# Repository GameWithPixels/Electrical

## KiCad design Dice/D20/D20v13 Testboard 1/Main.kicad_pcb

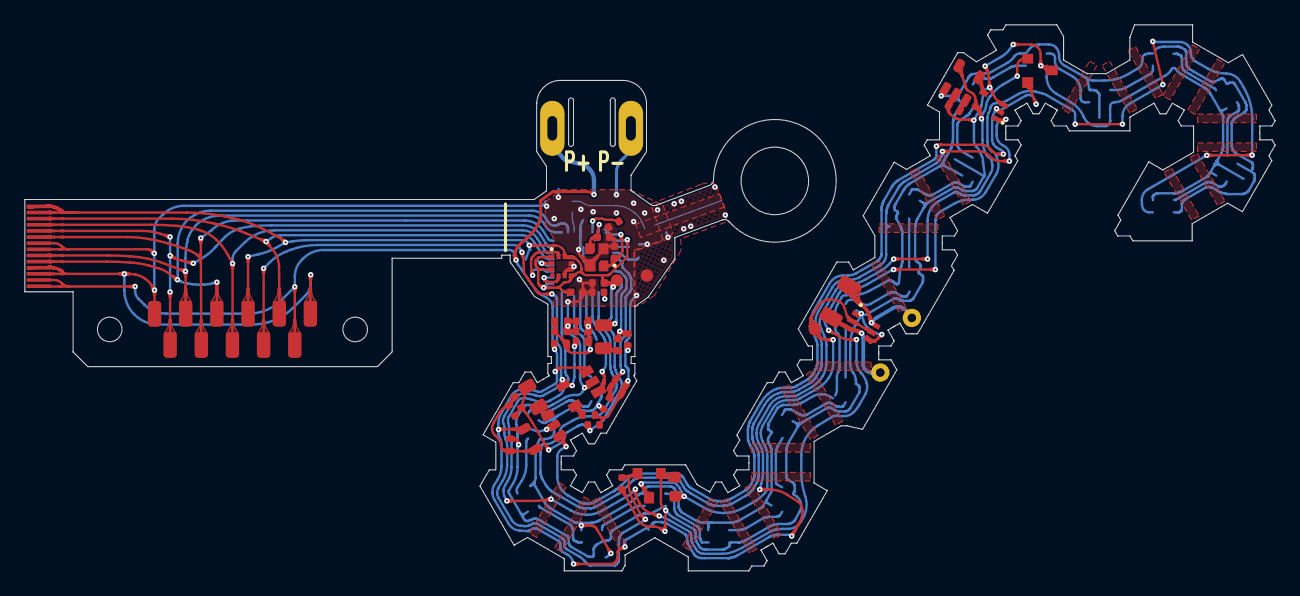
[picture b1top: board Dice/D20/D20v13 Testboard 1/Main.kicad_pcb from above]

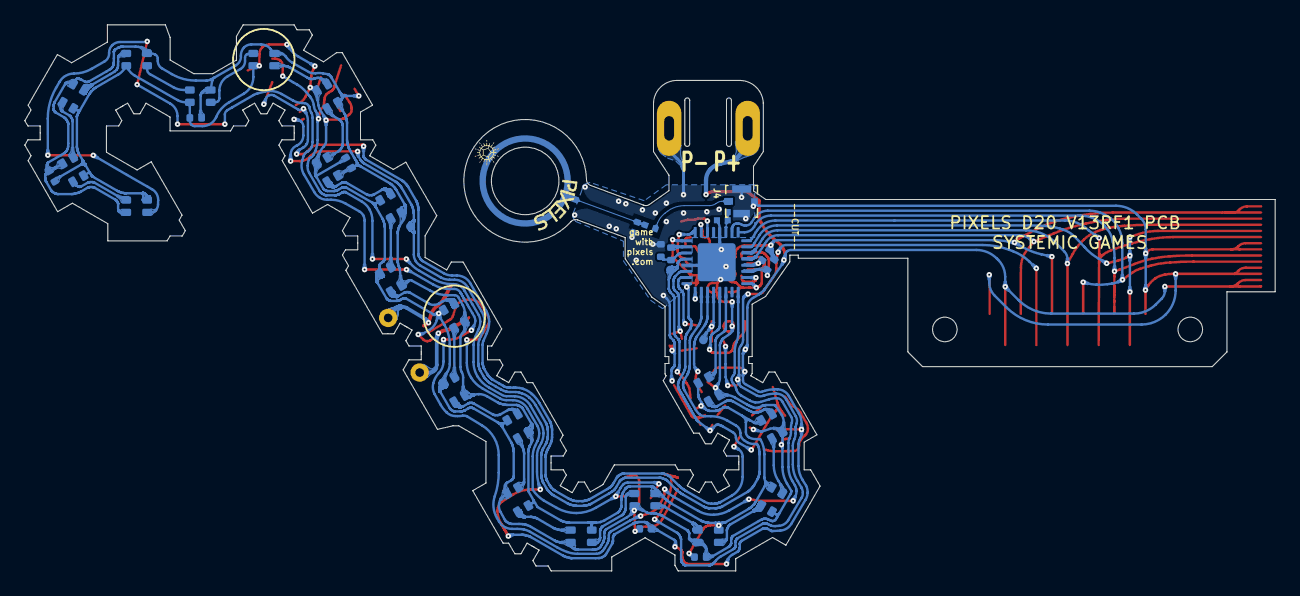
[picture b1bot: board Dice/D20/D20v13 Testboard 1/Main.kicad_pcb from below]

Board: 2 copper layers, 101.9 x 44.5 mm, 84 parts (40 on the bottom side), 61 nets.

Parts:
AE2: ARC; ARC_Antenna
C1, C4, C9, C15, C16, C18: 4.7uF 6.3V 20%; C_0402_1005Metric
C2, C5: 8pF 10V 10%; C_0402_1005Metric
C3, C10, C23, C24, C25: 0.1uF 10V 20%; C_0402_1005Metric
C6, C21, C22: 10nF 25V 10%; C_0402_1005Metric
C7: 100pF NP0 10V 5%; C_0402_1005Metric
C8: 0.8pF 10V 5% NP0; 0402_RF
C11: 1.8pF 10V 5% NP0; 0402_RF
C13: 4.7uF 25V 20%; C_0603_1608Metric
C17: 22pF 10V 5%; C_0402_1005Metric
C19: 33nF 50V 5% NP0; C_1206_3216Metric
D1: BAV99S; SOT-363_SC-70-6
D2, D3, D4, D5, D6, D7, D8, D9, D10, D11, D12, D13, D14, D15, D16, D17, D18, D19, D20, D21: TX1812Z_2020
J1: Conn_01x14; FPC_14
J2: Conn_01x11; FPC-POGO-11
J3: Conn_01x02; Hongjie 10100 Connector
J4: RECE.20369.001E.01; MFH3.RECE.20369.001E.01
L1: 10uH 100mA 10%; L_0805_2012Metric
L2: 15nH 100mA 5%; L_0402_1005Metric
L3: 4.7nH 5%; 0402_RF
L4: 2.2uH 20mA 10%; L_0805_2012Metric
L5: 3.9nH 5%; 0402_RF
P5: COILA; TestPoint_THTPad_D1.5mm_Drill0.7mm
P6: COILB; TestPoint_THTPad_D1.5mm_Drill0.7mm
R1, R7, R13: 4.02M 1%; R_0402_1005Metric
R2, R8, R14: 10M 1%; R_0402_1005Metric
R3: 10k 5%; R_0402_1005Metric
R4: 402k 1%; R_0402_1005Metric
R5, R9, R10: 100k 1%; R_0402_1005Metric
R6: 22k 1%; R_0402_1005Metric
R12, R16: 2.7k 5%; R_0402_1005Metric
U1: N52810_QFN32; QFN-32-1EP_5x5mm_P0.5mm_EP3.1x3.1mm
U2: KXTJ3-1057; LGA-12_2x2mm_P0.5mm
U3: PJ75AL50SA; SOT-23
U4: LN3435; SOT-23-5
U5: MCP73832T-2ACI/OT; SOT-23-5
U6: MT9700; SOT-23-5
U7: 74AHC1G08; SOT-353_SC-70-5
U8: TMR1366; SOT-23
W5: LED_EN; TEST_PIN
W12: VLED_S; TEST_PIN
W13: 5V_S; TEST_PIN
W16: VIN; TEST_PIN
W19: GND; TEST_PIN
W25: VDD; TEST_PIN
Y1: 32MHz 40ppm; Crystal_SMD_2016-4Pin_2.0x1.6mm

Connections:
+5V: C15.1, J2.4, R1.1, U3.2 (VOUT), U5.4 (VDD)
+BATT: C16.1, J1.1, J1.2, J2.2, J3.1, R7.1, U4.4 (VIN), U5.3 (VBAT), U6.5 (VIN), U7.5 (VCC), U8.1 (VCC)
/5V_SENSE: C21.1, R1.2, R2.2, U1.4 (P0.04/AIN2), W13.1
/ACC_INT: U1.10 (P0.12), U2.5 (INT)
/ANT_50: J4.4, L3.1, L5.2
/ANT_NRF: C8.1, L5.1, U1.19 (ANT)
/ARC_ANTENNA: AE2.1 (A), C11.1, L3.2
/LED_DATA: D2.1 (DIN), U1.6 (P0.06)
/LED_EN: U1.2 (P0.00/XL1), U7.1, W5.1
/LEDs/LED_RETURN: D21.3 (DOUT), U1.8 (P0.10)
/Power Supply/LED_EN_OUT: U6.4 (EN), U7.4
/Power Supply/MAG1_: U4.1 (CE), U7.2, U8.2 (OUT)
/SCL: R12.2, U1.11 (P0.14), U2.12 (SCL)
/SDA: R16.2, U1.12 (P0.15), U2.2 (SDA)
/STATS: U1.3 (P0.01/XL2), U5.1 (STAT)
/VBAT_SENSE: C22.1, R7.2, R8.1, U1.5 (P0.05/AIN3)
/VLED_SENSE: C6.1, R13.2, R14.1, U1.28 (P0.30/AIN6), W12.1
GND: C1.2, C2.1, C3.2, C4.2, C5.1, C6.2, C7.2, C8.2, C9.2, C10.2, C11.2, C13.2, C15.2, C16.2, C18.2, C21.2, C22.2, C23.2, C24.2, C25.2, D1.1 (A1), D1.4 (A3), D2.4 (GND), D3.4 (GND), D4.4 (GND), D5.4 (GND), D6.4 (GND), D7.4 (GND), D8.4 (GND), D9.4 (GND), D10.4 (GND), D11.4 (GND), D12.4 (GND), D13.4 (GND), D14.4 (GND), D15.4 (GND), D16.4 (GND), D17.4 (GND), D18.4 (GND), D19.4 (GND), D20.4 (GND), D21.4 (GND), J1.3, J1.4, J1.7, J1.8, J2.1, J2.11, J3.2, J4.1, J4.2, J4.3, R2.1, R3.2, R5.1, R6.2, R8.2, R9.1, R14.2, U1.20 (VSS), U1.29 (VSS), U1.33 (VSS), U2.6 (GND), U2.8 (GND), U2.9 (GND), U3.1 (VSS), U4.2 (GND), U5.2 (VSS), U6.2 (GND), U7.3 (GND), U8.3 (GND), W19.1, Y1.2, Y1.4
unnamed: C1.1, L2.2, U1.30 (DEC4)
unnamed: C2.2, U1.24 (XC2), Y1.1
unnamed: C3.1, U1.1 (DEC1)
unnamed: C5.2, U1.23 (XC1), Y1.3
unnamed: C7.1, U1.22 (DEC3)
unnamed: C17.2, R4.1, R5.2, U4.5 (FB)
unnamed: C19.1, D1.3 (K1A2), P5.1
unnamed: C19.2, D1.6 (K3A4), P6.1
unnamed: D2.3 (DOUT), D3.1 (DIN)
unnamed: D3.3 (DOUT), D4.1 (DIN)
unnamed: D4.3 (DOUT), D5.1 (DIN)
unnamed: D5.3 (DOUT), D6.1 (DIN)
unnamed: D6.3 (DOUT), D7.1 (DIN)
unnamed: D7.3 (DOUT), D8.1 (DIN)
unnamed: D8.3 (DOUT), D9.1 (DIN)
unnamed: D9.3 (DOUT), D10.1 (DIN)
unnamed: D10.3 (DOUT), D11.1 (DIN)
unnamed: D11.3 (DOUT), D12.1 (DIN)
unnamed: D12.3 (DOUT), D13.1 (DIN)
unnamed: D13.3 (DOUT), D14.1 (DIN)
unnamed: D14.3 (DOUT), D15.1 (DIN)
unnamed: D15.3 (DOUT), D16.1 (DIN)
unnamed: D16.3 (DOUT), D17.1 (DIN)
unnamed: D17.3 (DOUT), D18.1 (DIN)
unnamed: D18.3 (DOUT), D19.1 (DIN)
unnamed: D19.3 (DOUT), D20.1 (DIN)
unnamed: D20.3 (DOUT), D21.1 (DIN)
unnamed: L1.1, U1.31 (DCC)
unnamed: L1.2, L2.1
unnamed: L4.1, U4.3 (LX)
unnamed: R3.1, U6.3 (SET)
unnamed: R6.1, U5.5 (PROG)
unnamed: R9.2, R10.1, U1.27 (P0.28/AIN4)
unnamed: R10.2, U1.26 (P0.25)
RESET: J1.9, J2.8, U1.16 (P0.16)
RXI: J1.10, J2.10, U1.15 (P0.20/TCLK)
SWDCLK: J1.6, J2.9, U1.17 (SWDCLK)
SWDIO: J1.5, J2.7, U1.18 (SWDIO)
SWO: J1.11, J2.6, U1.14 (P0.18/TDATA0)
TXO: J1.12, J2.3, U1.13 (P0.16/TDATA1)
VDC: C9.1, C23.1, C24.1, C25.1, D2.2 (VCC), D3.2 (VCC), D4.2 (VCC), D5.2 (VCC), D6.2 (VCC), D7.2 (VCC), D8.2 (VCC), D9.2 (VCC), D10.2 (VCC), D11.2 (VCC), D12.2 (VCC), D13.2 (VCC), D14.2 (VCC), D15.2 (VCC), D16.2 (VCC), D17.2 (VCC), D18.2 (VCC), D19.2 (VCC), D20.2 (VCC), D21.2 (VCC), R13.1, U6.1 (VOUT)
VDD: C4.1, C10.1, C17.1, C18.1, J1.13, J1.14, J2.5, L4.2, R4.2, R12.1, R16.1, U1.9 (VDD), U1.25 (VDD), U1.32 (VDD), U2.1 (ADDR), U2.3 (IO_VDD), U2.7 (VDD), U2.10 (VDD), U2.11 (IO_VDD), W25.1
VEE: C13.1, D1.2 (K2), D1.5 (K4), U3.3 (VIN), W16.1

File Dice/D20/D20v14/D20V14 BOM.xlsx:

Item | Qty | Reference(s) | Value | Footprint | Generic OK | Manufacturer | Manufacturer Part Number
1 | 1 | AE1 | Antenna_Chip | Pixels-dice:CHIP_ANT | NO | Microgate | MGMA3216H2450-A02
2 | 4 | C1, C4, C15, C18 | 4.7uF 6.3V 20% | Pixels-dice:C_0402_1005Metric | YES | Murata | GRM155R60J475ME87D
3 | 2 | C2, C5 | 8pF 10V 10% | Pixels-dice:C_0402_1005Metric | YES | Murata | GRM1555C2A8R0DA01D
4 | 5 | C3, C10, C23, C24, C25 | 0.1uF 10V 20% | Pixels-dice:C_0402_1005Metric | YES | Murata | GRM155R61H104KE19D
5 | 3 | C6, C21, C22 | 10nF 25V 10% | Pixels-dice:C_0402_1005Metric | YES | Murata | GRM155R71H103KA88
6 | 1 | C7 | 100pF NP0 10V 5% | Pixels-dice:C_0402_1005Metric | YES | Murata | GCM1555C1H101JA16J
7 | 1 | C8 | 0.8pF 10V 5% C0G | Pixels-dice:0402_RF | YES | Murata | GRM1555C2AR80BA01D
8 | 2 | C9, C16 | 10uF 6.3V 20% | Pixels-dice:C_0402_1005Metric | YES | Murata | GRM155R60J106ME05J
10 | 1 | C12 | 0.5pF 10V 5% C0G | Pixels-dice:0402_RF | YES | Murata | GRM1555C1ER50WA01D
11 | 1 | C13 | 4.7uF 25V 20% | Capacitor_SMD:C_0603_1608Metric | YES | Murata | GRM188R61E475KE11D
12 | 1 | C17 | 22pF 10V 5% | Pixels-dice:C_0402_1005Metric | YES | Murata | GCM1555C1H220JA16J
13 | 1 | C19 | 33nF 50V 5% NP0 | Capacitor_SMD:C_1206_3216Metric | NO | Murata | GRM3195C1H333JA01J
14 | 1 | D1 | BAV99S | Package_TO_SOT_SMD:SOT-363_SC-70-6 | YES | Nexperia | BAV99S,115
15 | 20 | D2, D3, D4, D5, D6, D7, D8, D9, D10, D11, D12, D13, D14, D15, D16, D17, D18, D1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 | TX1812Z_2020 | Pixels-dice:TX1812Z_2020 | NO | TCWIN | TX1812Z 2020
20 | 1 | L1 | 10uH 100mA 20% | Inductor_SMD:L_0805_2012Metric | YES | Murata | LQM21FN100M80L
21 | 1 | L2 | 15nH 100mA 5% | Inductor_SMD:L_0402_1005Metric | YES | Murata | LQG15HS15NJ02D
22 | 1 | L3 | 1.8nH 5% | Pixels-dice:0402_RF | YES | Murata | LQG15HZ1N8C02D
23 | 1 | L4 | 2.2uH 20mA 10% | Inductor_SMD:L_0805_2012Metric | YES | Murata | LQM21DN2R2N00
24 | 1 | L5 | 3.9nH 5% | Pixels-dice:0402_RF | YES | Murata | LQG15HS3N9B02D
27 | 3 | R1, R7, R13 | 4.02M 1% | Pixels-dice:R_0402_1005Metric | YES | UNI-ROYAL(Uniroyal Elec) | 0402WGF4024TCE
28 | 3 | R2, R8, R14 | 10M 1% | Pixels-dice:R_0402_1005Metric | YES | Yageo | RC0402FR-0710ML
29 | 1 | R3 | 10k 5% | Pixels-dice:R_0402_1005Metric | YES | Yageo | RC0402JR-0710KL
30 | 1 | R4 | 402k 1% | Pixels-dice:R_0402_1005Metric | YES | Yageo | RC0402FR-07402KL
31 | 3 | R5, R9, R10 | 100k 1% | Pixels-dice:R_0402_1005Metric | YES | Vishay | CRCW0402100KFKEDC
32 | 1 | R6 | 22k 1% | Pixels-dice:R_0402_1005Metric | YES | Yageo | RC0402FR-0722KL
33 | 2 | R12, R16 | 2.7k 5% | Pixels-dice:R_0402_1005Metric | YES | Yageo | RC0402JR-072K7L
34 | 1 | U1 | N52810_QFN32 | Package_DFN_QFN:QFN-32-1EP_5x5mm_P0.5mm_EP3.1x3.1mm | NO | Nordic Semiconductor | NRF52810-QCAA-R
35 | 1 | U2 | KXTJ3-1057 | Package_LGA:LGA-12_2x2mm_P0.5mm | NO | Kionix | KXTJ3-1057
36 | 1 | U3 | PJ75AL50SA | Pixels-dice:SOT-23 | NO | PJSEMI | PJ75AL50SA
37 | 1 | U4 | LN3435 | Pixels-dice:SOT-23-5 | NO | NATLINEAR | LN3435
38 | 1 | U5 | MCP73832T-2ACI/OT | Package_TO_SOT_SMD:SOT-23-5 | NO | Microchip | MCP73832T-2ACI/OT
39 | 1 | U6 | MT9700 | Pixels-dice:SOT-23-5 | NO | XI'AN Aerosemi Tech | MT9700
40 | 1 | U7 | 74AHC1G08 | Pixels-dice:SOT-353_SC-70-5 | YES | UMW(Youtai Semiconductor Co., Ltd.) | SN74LVC1G08DCKR
41 | 1 | U8 | TMR1366 | Package_TO_SOT_SMD:SOT-23 | NO | Multi Dimension | TMR1366S
61 | 1 | Y1 | 32MHz 40ppm | Pixels-dice:Crystal_SMD_2016-4Pin_2.0x1.6mm | YES | Murata | XRCGB32M000F2P00R0

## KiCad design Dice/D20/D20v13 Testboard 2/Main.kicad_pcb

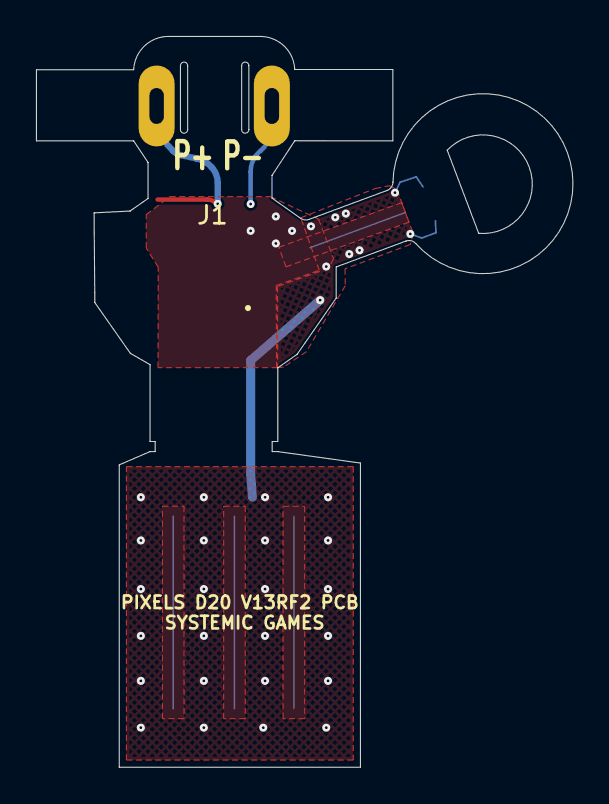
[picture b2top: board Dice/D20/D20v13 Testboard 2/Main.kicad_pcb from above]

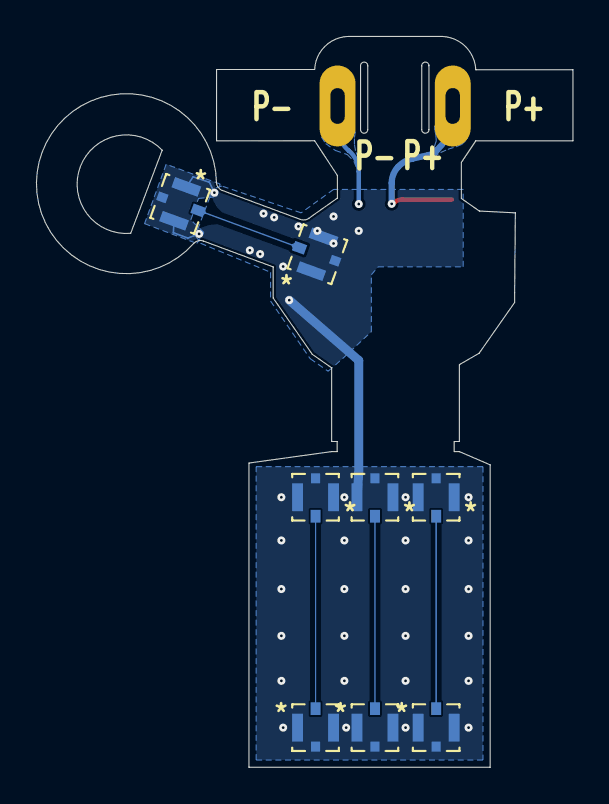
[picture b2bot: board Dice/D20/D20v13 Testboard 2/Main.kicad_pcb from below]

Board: 2 copper layers, 29.8 x 40.6 mm, 9 parts (8 on the bottom side), 5 nets.

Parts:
J1: Conn_01x02; Hongjie 10100 Connector
J2, J3, J4, J5, J6, J7, J8, J9: RECE.20369.001E.01; MFH3.RECE.20369.001E.01

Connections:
/ANT_0.7: J2.4, J3.4
/ANT_0.8: J4.4, J5.4
/ANT_0.9: J8.4, J9.4
/ARC_ANTENNA: J6.4, J7.4
GND: J2.1, J2.2, J2.3, J3.1, J3.2, J3.3, J4.1, J4.2, J4.3, J5.1, J5.2, J5.3, J6.1, J6.2, J6.3, J7.1, J7.2, J7.3, J8.1, J8.2, J8.3, J9.1, J9.2, J9.3
